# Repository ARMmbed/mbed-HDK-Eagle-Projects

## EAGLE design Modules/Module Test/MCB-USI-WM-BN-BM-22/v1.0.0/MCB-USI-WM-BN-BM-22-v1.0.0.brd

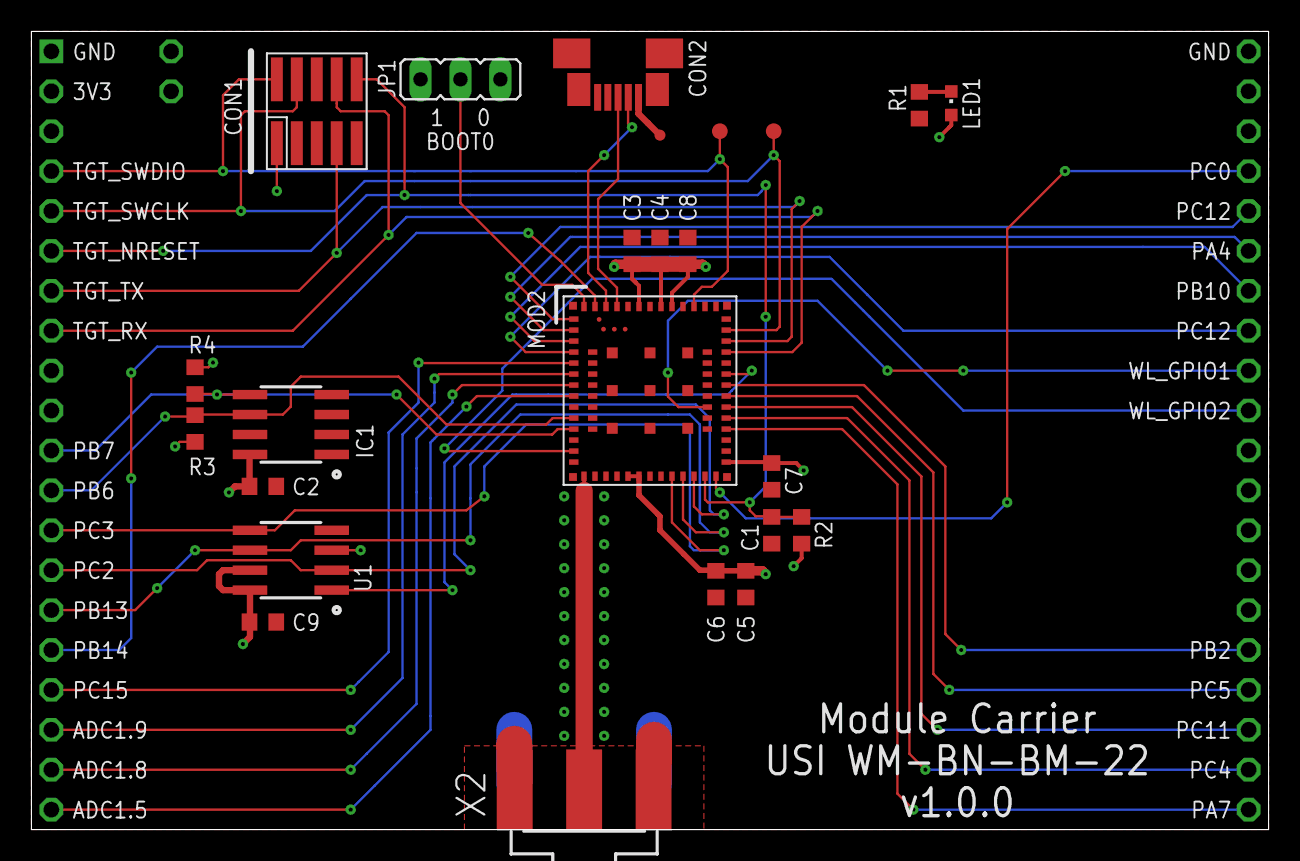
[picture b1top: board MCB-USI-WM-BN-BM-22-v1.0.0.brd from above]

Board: 2 copper layers, 78.7 x 50.8 mm, 28 parts (0 on the bottom side), 36 nets.

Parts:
C1, C2, C3, C4, C5, C6, C7, C8, C9: 100nF; 0603
CON1: SWD-10/TC2050_SMD; FTSH-105-02
CON2: 47346-0001; USB-MICRO-B-H
IC1: ATECC608A; SO8
JP1: BOOT0; JP2
LED1: RED; CHIPLED_0603
MOD1: MODULE_DAUGHTER
MOD2: USI-WM-BN-BM-22
R1: 1k; 0603
R2: 10k; 0603
R3, R4: 4k7; 0603
SS1: FLOSSICORN0.5; FLOSSICORN-0.5
TP1, TP2: TEST-POINT-50R-PTH; TP50-PTH
TP3, TP4: PTR1TP10R; TP10R
TP5: PTR1TP07R; TP07R
U1: MX25R3235FM1IH0; SO8
X2: SMA-142-0701-801/806; J502-ND-142-0701-801/806

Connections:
+3.3V_TGT: C2.1, C3.1, C4.1, C5.1, C6.1, C7.1, C8.1, C9.1, CON1.1, IC1.8, JP1.3, LED1.A, MOD1.2, MOD2.19, MOD2.20, MOD2.28, MOD2.46, MOD2.47, MOD2.49, R2.2, R3.2, R4.2, TP1.TP, U1.3, U1.7, U1.8
ADC1.5: MOD1.20, MOD2.8
ADC1.8: MOD1.19, MOD2.7
ADC1.9: MOD1.18, MOD2.6
BOOT0: JP1.2, MOD2.54
GND: C1.2, C2.2, C3.2, C4.2, C5.2, C6.2, C7.2, C8.2, C9.2, CON1.3, CON1.5, CON1.9, CON2.GND, IC1.4, JP1.1, MOD1.1, MOD1.40, MOD2.12, MOD2.14, MOD2.16, MOD2.17, MOD2.18, MOD2.21, MOD2.29, MOD2.30, MOD2.37, MOD2.45, MOD2.48, MOD2.50, MOD2.55, MOD2.56, MOD2.57, MOD2.58, MOD2.59, MOD2.60, MOD2.61, MOD2.62, MOD2.63, MOD2.64, MOD2.65, MOD2.66, MOD2.67, MOD2.68, MOD2.70, MOD2.74, MOD2.83, R1.1, TP2.TP, U1.4, X2.G@1, X2.G@2, X2.G@3, X2.G@4
unnamed: CON2.D+, MOD2.51
unnamed: CON2.D-, MOD2.52
unnamed: CON2.VBUS, TP5.TP
unnamed: MOD2.15, X2.1
PA4: MOD1.35, MOD2.2
PA6: MOD2.36, U1.1
PA7: MOD1.21, MOD2.31
PA_1: LED1.C, R1.2
PB2: MOD1.25, MOD2.35
PB6: IC1.6, MOD1.12, MOD2.10, R3.1
PB7: IC1.5, MOD1.11, MOD2.11, R4.1
PB10: MOD1.34, MOD2.3
PB12: MOD1.36, MOD2.1
PB13: MOD1.15, MOD2.24, U1.6
PB14: MOD1.16, MOD2.53
PC0: MOD1.37, MOD2.27
PC2: MOD1.14, MOD2.25, U1.2
PC3: MOD1.13, MOD2.23, U1.5
PC4: MOD1.22, MOD2.32
PC5: MOD1.24, MOD2.34
PC11: MOD1.23, MOD2.33
PC12: MOD1.33, MOD2.4
PC15: MOD1.17, MOD2.5
TGT_NRESET: C1.1, CON1.10, MOD1.6, MOD2.26, R2.1
TGT_RX: CON1.8, MOD1.8, MOD2.38
TGT_SWCLK: CON1.4, MOD1.5, MOD2.40, TP4.TP
TGT_SWDIO: CON1.2, MOD1.4, MOD2.44, TP3.TP
TGT_TX: CON1.7, MOD1.7, MOD2.39
WL_GPIO1: MOD1.32, MOD2.78
WL_GPIO2: MOD1.31, MOD2.13

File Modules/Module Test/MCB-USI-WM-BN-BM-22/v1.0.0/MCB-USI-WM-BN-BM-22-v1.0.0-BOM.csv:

"Qty";"Value";"Device";"Package";"Parts";"Description";"MF";"MFN";"MPN";"OC-DIGIKEY";"OC-MOUSER";"OC-NEWARK";"OC_FARNELL";"OC_NEWARK";"TP_SIGNAL_NAME";
"9";"100nF";"CAPACITOR0603";"0603";"C1, C2, C3, C4, C5, C6, C7, C8, C9";"Capacitor";"";"";"";"";"";"";"";"";"";
"1";"10k";"RESISTOR0603";"0603";"R2";"Resistor";"";"";"";"";"";"";"";"";"";
"1";"1k";"RESISTOR0603";"0603";"R1";"Resistor";"";"";"";"";"";"";"";"";"";
"1";"47346-0001";"47346-0001";"USB-MICRO-B-H";"CON2";"USB Receptacle Horizontal Micro Type B";"MOLEX";"47346-0001";"";"";"538-47346-0001";"1568026";"";"";"";
"2";"4k7";"RESISTOR0603";"0603";"R3, R4";"Resistor";"";"";"";"";"";"";"";"";"";
"1";"ATECC608A";"ATECC608A";"SO8";"IC1";"";"";"";"";"";"";"";"";"";"";
"1";"BOOT0";"JP2E";"JP2";"JP1";"JUMPER";"";"";"";"";"";"";"";"";"";
"1";"FLOSSICORN0.5";"FLOSSICORN0.5";"FLOSSICORN-0.5";"SS1";"";"";"";"";"";"";"";"";"";"";
"1";"MODULE_DAUGHTER";"MODULE_DAUGHTER";"MODULE_DAUGHTER";"MOD1";"";"";"";"";"";"";"";"";"";"";
"1";"MX25R3235FM1IH0";"MX25R3235FM1IH0";"SO8";"U1";"Serial Flash 32 Mb 80 Mhz";"Macronix";"MX25R3235FM2IH0";"";"1092-1174-ND";"";"";"";"";"";
"1";"PTR1TP07R";"PTR1TP07R";"TP07R";"TP5";"TEST PIN";"";"";"";"";"";"";"";"";"";
"2";"PTR1TP10R";"PTR1TP10R";"TP10R";"TP3, TP4";"TEST PIN";"";"";"";"";"";"";"";"";"";
"1";"RED";"SMD_LED0603";"CHIPLED_0603";"LED1";"LED SMD, Colour Red";"Wurth Electronics Inc";"150060RS75000";"";"732-4978-1-ND";"710-150060RS75000";"2322071";"";"";"";
"1";"SMA-142-0701-801/806";"SMA-142-0701-801/806";"J502-ND-142-0701-801/806";"X2";"SMA 50 Ohm End Launch Jack Receptacle - Round Contact";"JOHNSON COMPONENTS";"";"142-0701-801";"";"";"";"1608592";"90F2624";"";
"1";"SWD-10/TC2050_SMD";"SWD-10/TC2050_SMD";"FTSH-105-02";"CON1";"1mm pitch 10-Pin Cortex Programming Header with optional TC2050 footprint solderless interchangeable";"";"";"";"";"";"";"";"";"";
"2";"TEST-POINT-50R-PTH";"TEST-POINT-50R-PTH";"TP50-PTH";"TP1, TP2";"";"";"";"";"";"";"";"";"";"";
"1";"USI-WM-BN-BM-22";"USI-WM-BN-BM-22";"USI-WM-BN-BM-22";"MOD2";"";"";"";"";"";"";"";"";"";"";

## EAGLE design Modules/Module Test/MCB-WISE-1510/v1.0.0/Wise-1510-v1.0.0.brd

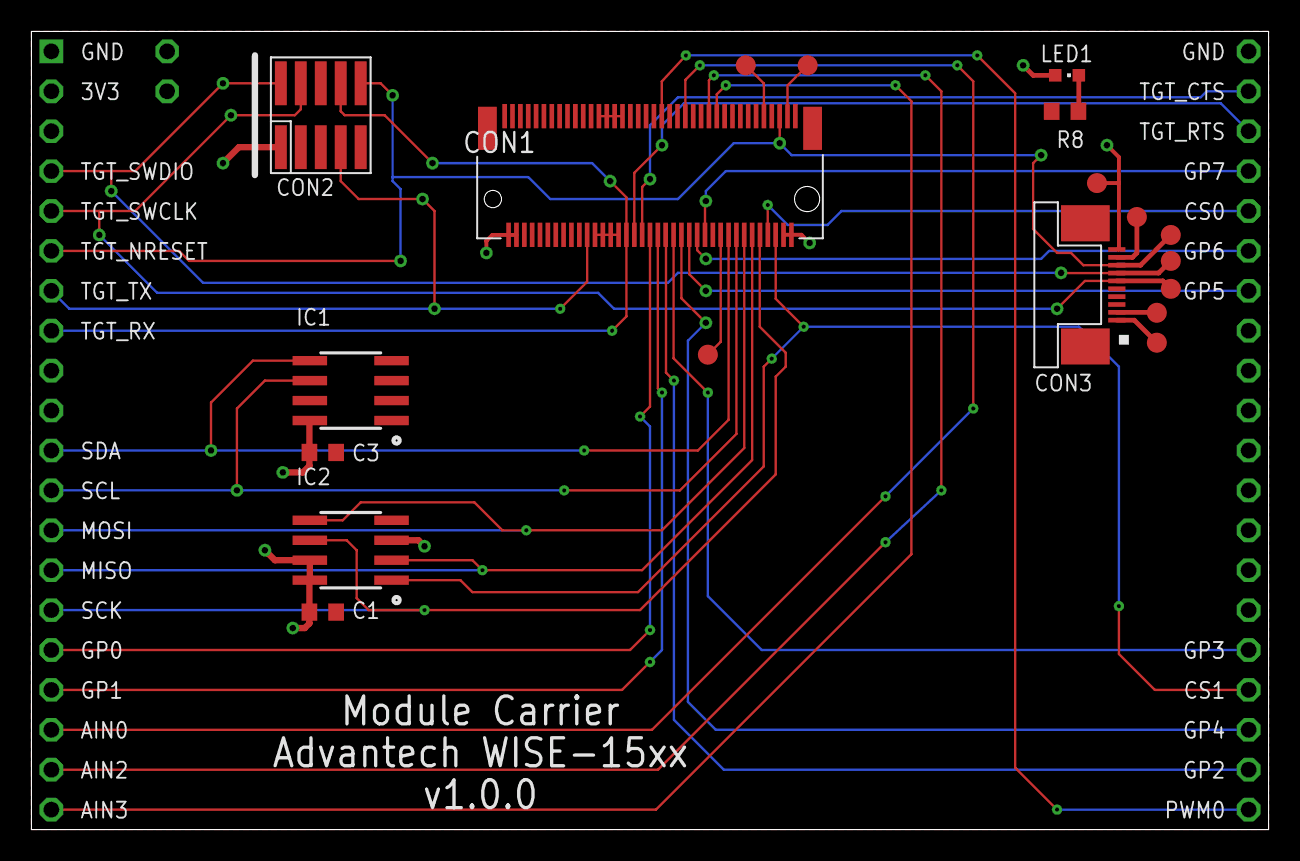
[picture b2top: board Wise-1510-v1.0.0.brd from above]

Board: 2 copper layers, 78.7 x 50.8 mm, 22 parts (0 on the bottom side), 36 nets.

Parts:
C1, C3: 100nF; 0603
CON1: WISE-1510_E; MDT420E02001
CON2: SWD-10/TC2050_SMD; FTSH-105-02
CON3: TE-1-1734592-0
IC1: ATECC608A; SO8
IC2: MX25R3235FM1IH0; SO8
LED1: RED; CHIPLED_0603
R8: 1k; 0603
TP1, TP2: TEST-POINT-50R-PTH; TP50-PTH
TP3, TP4, TP5, TP6, TP7, TP8, TP9, TP10, TP11, TP12: PTR1B1,27; B1,27
U$1: MODULE_DAUGHTER

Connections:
+3.3V_TGT: C1.1, C3.1, CON1.2, CON1.4, CON1.72, CON1.74, CON2.1, CON3.10, IC1.8, IC2.3, IC2.7, IC2.8, LED1.A, TP1.TP, TP12.TP, U$1.2
AIN0: CON1.47, U$1.18
AIN2: CON1.53, U$1.19
AIN3: CON1.55, U$1.20
BOOT_0: CON3.9, TP8.TP
CS0: CON1.68, U$1.36
CS1: CON1.70, IC2.1, U$1.24
GND: C1.2, C3.2, CON1.1, CON1.7, CON1.18, CON1.33, CON1.39, CON1.45, CON1.51, CON1.57, CON1.63, CON1.69, CON1.75, CON1.H1, CON1.H2, CON2.3, CON2.5, CON2.9, CON3.3, IC1.4, IC2.4, R8.1, TP2.TP, U$1.1, U$1.40
GP0: CON1.38, U$1.16
GP1: CON1.40, U$1.17
GP2: CON1.42, U$1.22
GP3: CON1.44, U$1.25
GP4: CON1.46, U$1.23
GP5: CON1.48, U$1.34
GP6: CON1.50, U$1.35
GP7: CON1.52, U$1.37
KEY: CON1.24, CON1.25, CON1.26, CON1.27, CON1.28, CON1.29, CON1.30, CON1.31
MISO: CON1.64, IC2.2, U$1.14
MOSI: CON1.62, IC2.5, U$1.13
unnamed: CON3.1, TP7.TP
unnamed: CON3.2, TP6.TP
unnamed: CON1.56, TP9.TP
unnamed: CON1.67, TP10.TP
unnamed: CON1.73, TP11.TP
PA_1: LED1.C, R8.2
PWM0: CON1.41, U$1.21
SCK: CON1.66, IC2.6, U$1.15
SCL: CON1.60, IC1.6, U$1.12
SDA: CON1.58, IC1.5, U$1.11
TGT_CTS: CON1.36, U$1.39
TGT_NRESET: CON1.71, CON2.10, CON3.8, TP5.TP, U$1.6
TGT_RTS: CON1.34, U$1.38
TGT_RX: CON1.32, CON2.8, U$1.8
TGT_SWCLK: CON2.4, CON3.6, TP3.TP, U$1.5
TGT_SWDIO: CON2.2, CON3.7, TP4.TP, U$1.4
TGT_TX: CON1.22, CON2.7, U$1.7

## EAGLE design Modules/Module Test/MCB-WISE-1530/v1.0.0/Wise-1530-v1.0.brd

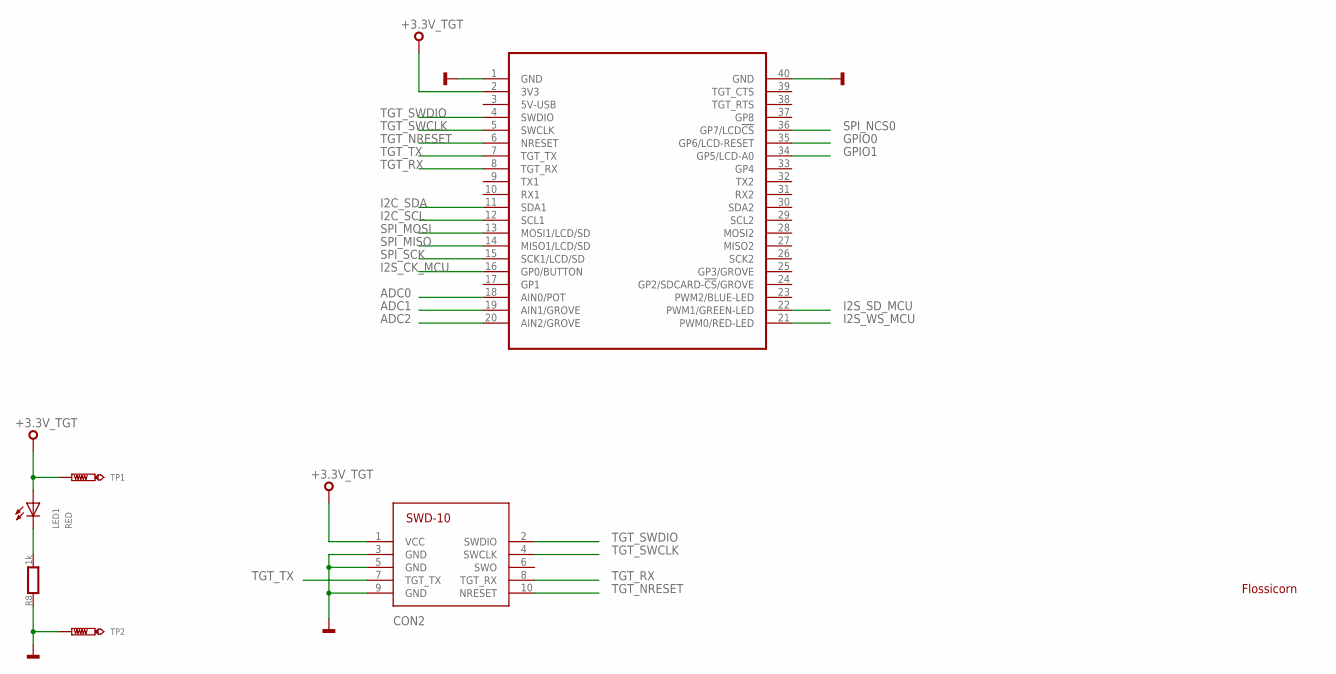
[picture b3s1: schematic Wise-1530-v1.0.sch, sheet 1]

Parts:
CON2: SWD-10/TC2050_SMD; FTSH-105-02
LED1: RED; CHIPLED_0603
MOD2: MODULE_DAUGHTER
R8: 1k; 0603
SS1: FLOSSICORN0.25; FLOSSICORN-0.25
TP1, TP2: TEST-POINT-50R-PTH; TP50-PTH

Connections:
+3.3V_TGT: CON2.1 (VCC), LED1.A, MOD2.2 (3V3), TP1.TP; also elsewhere on the board
ADC0: MOD2.18 (AIN0/POT); also elsewhere on the board
ADC1: MOD2.19 (AIN1/GROVE); also elsewhere on the board
ADC2: MOD2.20 (AIN2/GROVE); also elsewhere on the board
GND: CON2.3 (GND), CON2.5 (GND), CON2.9 (GND), MOD2.1 (GND), MOD2.40 (GND), R8.1, TP2.TP; also elsewhere on the board
GPIO0: MOD2.35 (GP6/LCD-RESET); also elsewhere on the board
GPIO1: MOD2.34 (GP5/LCD-A0); also elsewhere on the board
I2C_SCL: MOD2.12 (SCL1); also elsewhere on the board
I2C_SDA: MOD2.11 (SDA1); also elsewhere on the board
I2S_CK_MCU: MOD2.16 (GP0/BUTTON); also elsewhere on the board
I2S_SD_MCU: MOD2.22 (PWM1/GREEN-LED); also elsewhere on the board
I2S_WS_MCU: MOD2.21 (PWM0/RED-LED); also elsewhere on the board
PA_1: LED1.C, R8.2
SPI_MISO: MOD2.14 (MISO1/LCD/SD); also elsewhere on the board
SPI_MOSI: MOD2.13 (MOSI1/LCD/SD); also elsewhere on the board
SPI_NCS0: MOD2.36 (GP7/LCD!CS); also elsewhere on the board
SPI_SCK: MOD2.15 (SCK1/LCD/SD); also elsewhere on the board
TGT_NRESET: CON2.10 (NRESET), MOD2.6 (NRESET); also elsewhere on the board
TGT_RX: CON2.8 (TGT_RX), MOD2.8 (TGT_RX); also elsewhere on the board
TGT_SWCLK: CON2.4 (SWCLK), MOD2.5 (SWCLK); also elsewhere on the board
TGT_SWDIO: CON2.2 (SWDIO), MOD2.4 (SWDIO); also elsewhere on the board
TGT_TX: CON2.7 (TGT_TX), MOD2.7 (TGT_TX); also elsewhere on the board

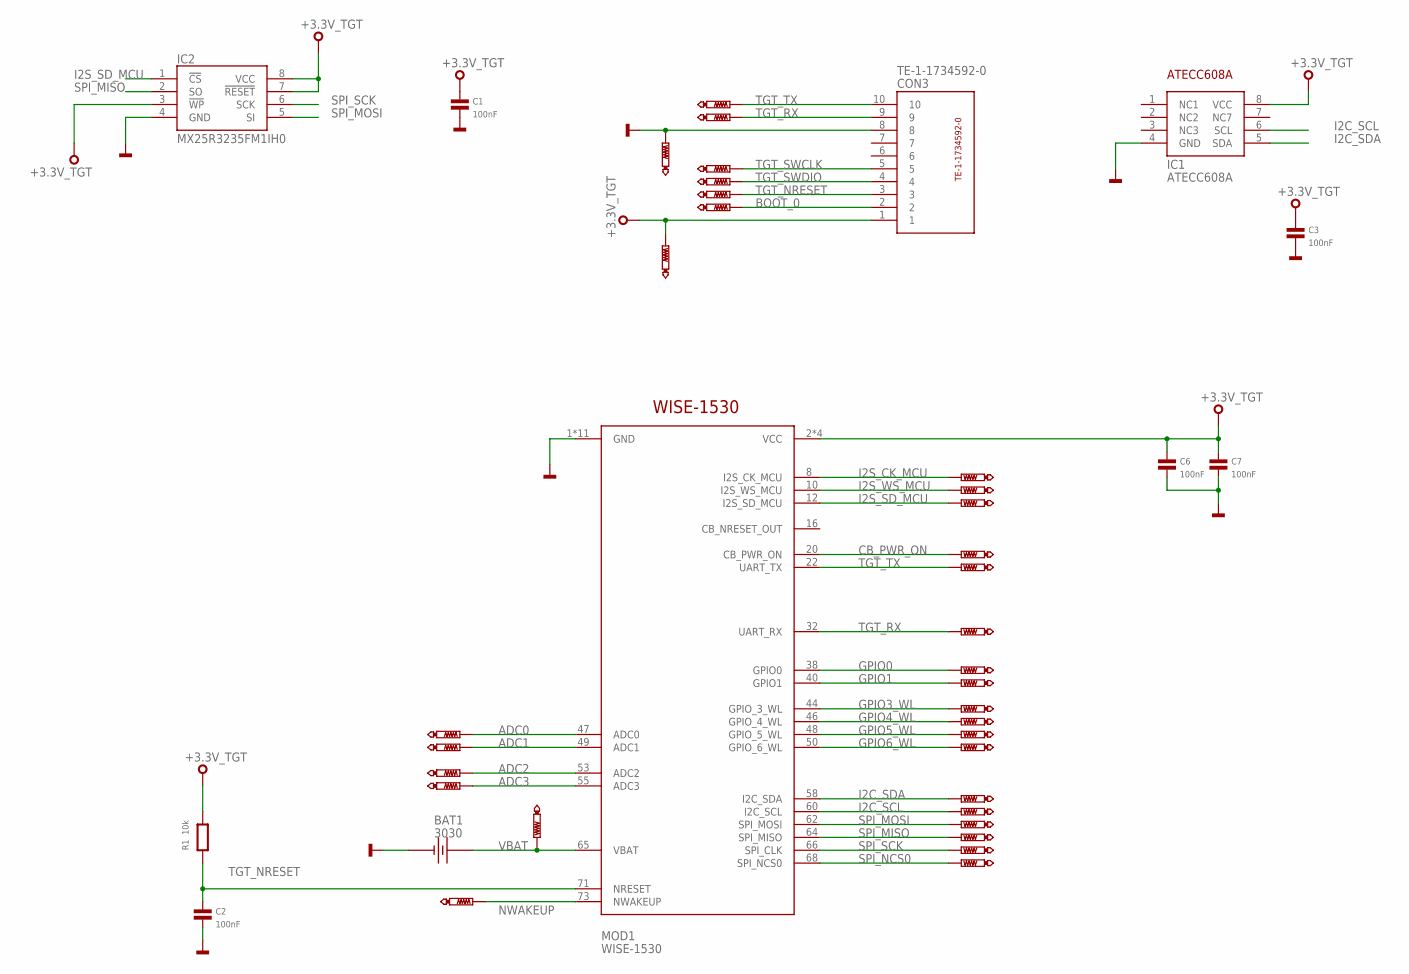
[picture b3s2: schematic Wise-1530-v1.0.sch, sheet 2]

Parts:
BAT1: 3030
C1, C2, C3, C6, C7: 100nF; 0603
CON3: TE-1-1734592-0
IC1: ATECC608A; SO8
IC2: MX25R3235FM1IH0; SO8
MOD1: WISE-1530; MDT420E02001
R1: 10k; 0603
TP3, TP4, TP5, TP6, TP7, TP8, TP12, TP13: PTR1TP08R; TP08R
TP9, TP10, TP11, TP14, TP15, TP16, TP17, TP18, TP19, TP20, TP21, TP22, TP23, TP24, TP25, TP26, TP27, TP28, TP29, TP30, TP31, TP32, TP33, TP34: PTR1TP07R; TP07R

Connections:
+3.3V_TGT: C1.1, C3.1, C6.1, C7.1, CON3.1, IC1.8 (VCC), IC2.3 (!WP), IC2.7 (!RESET), IC2.8 (VCC), MOD1.2 (VCC), MOD1.4 (VCC), MOD1.72 (VCC), MOD1.74 (VCC), R1.2, TP12.TP; also elsewhere on the board
ADC0: MOD1.47 (ADC0), TP29.TP; also elsewhere on the board
ADC1: MOD1.49 (ADC1), TP30.TP; also elsewhere on the board
ADC2: MOD1.53 (ADC2), TP31.TP; also elsewhere on the board
ADC3: MOD1.55 (ADC3), TP32.TP
BOOT_0: CON3.2, TP8.TP
CB_PWR_ON: MOD1.20 (CB_PWR_ON), TP14.TP
GND: BAT1.-, C1.2, C2.2, C3.2, C6.2, C7.2, CON3.8, IC1.4 (GND), IC2.4 (GND), MOD1.1 (GND), MOD1.7 (GND), MOD1.18 (GND), MOD1.33 (GND), MOD1.39 (GND), MOD1.45 (GND), MOD1.51 (GND), MOD1.57 (GND), MOD1.63 (GND), MOD1.69 (GND), MOD1.75 (GND), TP13.TP; also elsewhere on the board
GPIO0: MOD1.38 (GPIO0), TP27.TP; also elsewhere on the board
GPIO1: MOD1.40 (GPIO1), TP26.TP; also elsewhere on the board
GPIO3_WL: MOD1.44 (GPIO_3_WL), TP25.TP
GPIO4_WL: MOD1.46 (GPIO_4_WL), TP24.TP
GPIO5_WL: MOD1.48 (GPIO_5_WL), TP23.TP
GPIO6_WL: MOD1.50 (GPIO_6_WL), TP22.TP
I2C_SCL: IC1.6 (SCL), MOD1.60 (I2C_SCL), TP20.TP; also elsewhere on the board
I2C_SDA: IC1.5 (SDA), MOD1.58 (I2C_SDA), TP21.TP; also elsewhere on the board
I2S_CK_MCU: MOD1.8 (I2S_CK_MCU), TP9.TP; also elsewhere on the board
I2S_SD_MCU: IC2.1 (!CS), MOD1.12 (I2S_SD_MCU), TP11.TP; also elsewhere on the board
I2S_WS_MCU: MOD1.10 (I2S_WS_MCU), TP10.TP; also elsewhere on the board
NWAKEUP: MOD1.73 (NWAKEUP), TP34.TP
SPI_MISO: IC2.2 (SO), MOD1.64 (SPI_MISO), TP18.TP; also elsewhere on the board
SPI_MOSI: IC2.5 (SI), MOD1.62 (SPI_MOSI), TP19.TP; also elsewhere on the board
SPI_NCS0: MOD1.68 (SPI_NCS0), TP16.TP; also elsewhere on the board
SPI_SCK: IC2.6 (SCK), MOD1.66 (SPI_CLK), TP17.TP; also elsewhere on the board
TGT_NRESET: C2.1, CON3.3, MOD1.71 (NRESET), R1.1, TP5.TP; also elsewhere on the board
TGT_RX: CON3.9, MOD1.32 (UART_RX), TP6.TP, TP28.TP; also elsewhere on the board
TGT_SWCLK: CON3.5, TP3.TP; also elsewhere on the board
TGT_SWDIO: CON3.4, TP4.TP; also elsewhere on the board
TGT_TX: CON3.10, MOD1.22 (UART_TX), TP7.TP, TP15.TP; also elsewhere on the board
VBAT: BAT1.+1 (+), BAT1.+2 (+), MOD1.65 (VBAT), TP33.TP

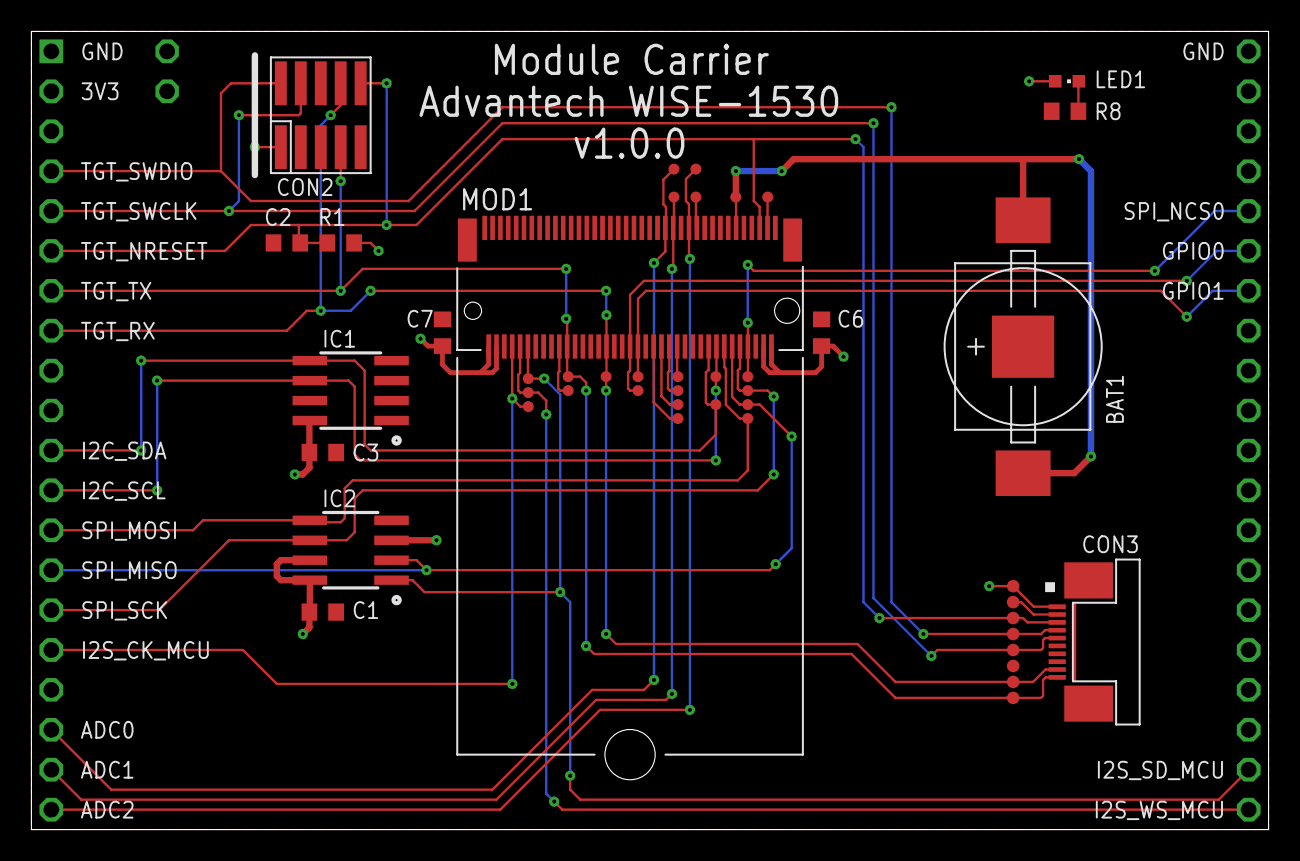
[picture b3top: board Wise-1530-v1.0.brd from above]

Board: 2 copper layers, 78.7 x 50.8 mm, 50 parts (0 on the bottom side), 31 nets.

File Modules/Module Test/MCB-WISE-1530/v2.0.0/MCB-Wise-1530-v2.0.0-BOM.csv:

"Qty";"Value";"Device";"Package";"Parts";"Description";"MF";"MFN";"OC-DIGIKEY";"OC-MOUSER";"OC-NEWARK";"TP_SIGNAL_NAME";
"5";"100nF";"CAPACITOR0603";"0603";"C1, C2, C3, C6, C7";"Capacitor";"";"";"";"";"";"";
"1";"10k";"RESISTOR0603";"0603";"R1";"Resistor";"";"";"";"";"";"";
"1";"1k";"RESISTOR0603";"0603";"R8";"Resistor";"";"";"";"";"";"";
"1";"3030";"3030";"3030";"BAT1";"CR927, CR1025 Battery Holder for 9-10mm Cells-Tin Nickel Plated SMD";"Keystone";"3030";"36-3030-ND";"534-3030";"39T8899";"";
"1";"ATECC608A";"ATECC608A";"SO8";"IC1";"";"";"";"";"";"";"";
"1";"FLOSSICORN0.25";"FLOSSICORN0.25";"FLOSSICORN-0.25";"SS1";"";"";"";"";"";"";"";
"1";"MODULE_DAUGHTER";"MODULE_DAUGHTER";"MODULE_DAUGHTER";"MOD2";"";"";"";"";"";"";"";
"1";"MX25R3235FM1IH0";"MX25R3235FM1IH0";"SO8";"IC2";"Serial Flash 32 Mb 80 Mhz";"Macronix";"MX25R3235FM1IH0";"1092-1175-ND";"";"";"";
"24";"PTR1TP07R";"PTR1TP07R";"TP07R";"TP9, TP10, TP11, TP14, TP15, TP16, TP17, TP18, TP19, TP20, TP21, TP22, TP23, TP24, TP25, TP26, TP27, TP28, TP29, TP30, TP31, TP32, TP33, TP34";"TEST PIN";"";"";"";"";"";"";
"8";"PTR1TP08R";"PTR1TP08R";"TP08R";"TP3, TP4, TP5, TP6, TP7, TP8, TP12, TP13";"TEST PIN";"";"";"";"";"";"";
"1";"RED";"SMD_LED0603";"CHIPLED_0603";"LED1";"LED SMD, Colour Red";"Wurth Electronics Inc";"150060RS75000";"732-4978-1-ND";"710-150060RS75000";"2322071";"";
"1";"SWD-10/TC2050_SMD";"SWD-10/TC2050_SMD";"FTSH-105-02";"CON2";"1mm pitch 10-Pin Cortex Programming Header with optional TC2050 footprint solderless interchangeable";"";"";"";"";"";"";
"1";"TE-1-1734592-0";"TE-1-1734592-0";"TE-1-1734592-0";"CON3";"";"";"";"";"";"";"";
"2";"TEST-POINT-50R-PTH";"TEST-POINT-50R-PTH";"TP50-PTH";"TP1, TP2";"";"";"";"";"";"";"";
"1";"WISE-1530";"WISE-1530";"MDT420E02001";"MOD1";"";"";"";"";"";"";"";

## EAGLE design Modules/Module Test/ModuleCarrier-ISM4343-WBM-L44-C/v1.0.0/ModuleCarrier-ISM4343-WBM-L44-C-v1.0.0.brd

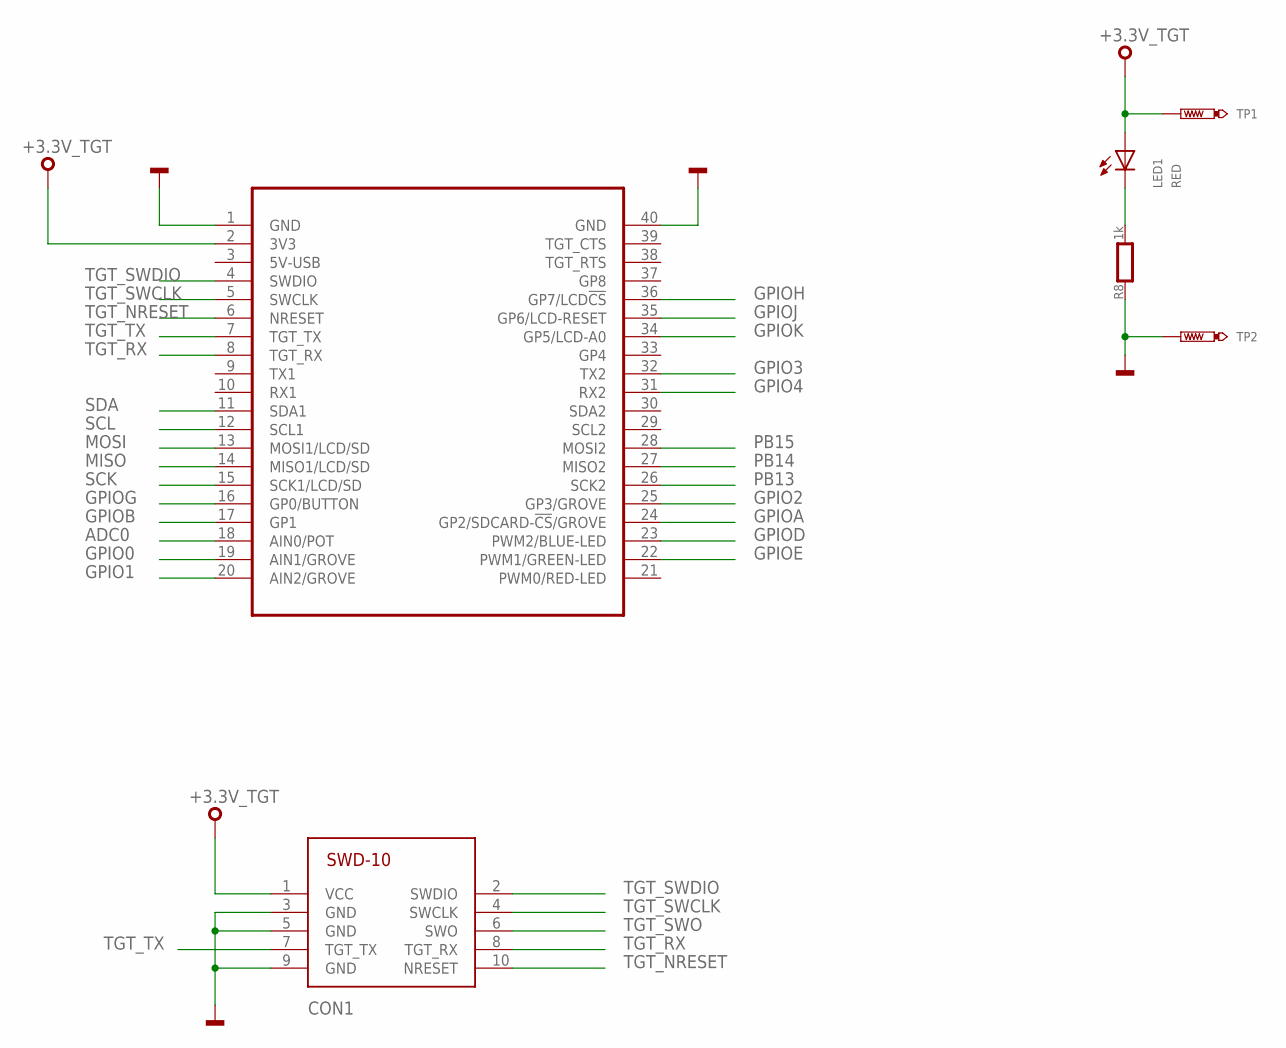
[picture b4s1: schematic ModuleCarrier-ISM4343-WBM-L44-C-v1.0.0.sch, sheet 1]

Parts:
CON1: SWD-10/TC2050_SMD; FTSH-105-02
LED1: RED; CHIPLED_0603
MOD2: MODULE_DAUGHTER
R8: 1k; 0603
TP1, TP2: TEST-POINT-50R-PTH; TP50-PTH

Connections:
+3.3V_TGT: CON1.1 (VCC), LED1.A, MOD2.2 (3V3), TP1.TP; also elsewhere on the board
ADC0: MOD2.18 (AIN0/POT)
GND: CON1.3 (GND), CON1.5 (GND), CON1.9 (GND), MOD2.1 (GND), MOD2.40 (GND), R8.1, TP2.TP; also elsewhere on the board
GPIO0: MOD2.19 (AIN1/GROVE)
GPIO1: MOD2.20 (AIN2/GROVE)
GPIO2: MOD2.25 (GP3/GROVE)
GPIO3: MOD2.32 (TX2)
GPIO4: MOD2.31 (RX2)
GPIOA: MOD2.24 (GP2/SDCARD-!CS!/GROVE)
GPIOB: MOD2.17 (GP1)
GPIOD: MOD2.23 (PWM2/BLUE-LED)
GPIOE: MOD2.22 (PWM1/GREEN-LED)
GPIOG: MOD2.16 (GP0/BUTTON)
GPIOH: MOD2.36 (GP7/LCD!CS)
GPIOJ: MOD2.35 (GP6/LCD-RESET)
GPIOK: MOD2.34 (GP5/LCD-A0)
MISO: MOD2.14 (MISO1/LCD/SD); also elsewhere on the board
MOSI: MOD2.13 (MOSI1/LCD/SD); also elsewhere on the board
PA_1: LED1.C, R8.2
PB13: MOD2.26 (SCK2)
PB14: MOD2.27 (MISO2)
PB15: MOD2.28 (MOSI2)
SCK: MOD2.15 (SCK1/LCD/SD); also elsewhere on the board
SCL: MOD2.12 (SCL1); also elsewhere on the board
SDA: MOD2.11 (SDA1); also elsewhere on the board
TGT_NRESET: CON1.10 (NRESET), MOD2.6 (NRESET)
TGT_RX: CON1.8 (TGT_RX), MOD2.8 (TGT_RX)
TGT_SWCLK: CON1.4 (SWCLK), MOD2.5 (SWCLK)
TGT_SWDIO: CON1.2 (SWDIO), MOD2.4 (SWDIO)
TGT_SWO: CON1.6 (SWO)
TGT_TX: CON1.7 (TGT_TX), MOD2.7 (TGT_TX)

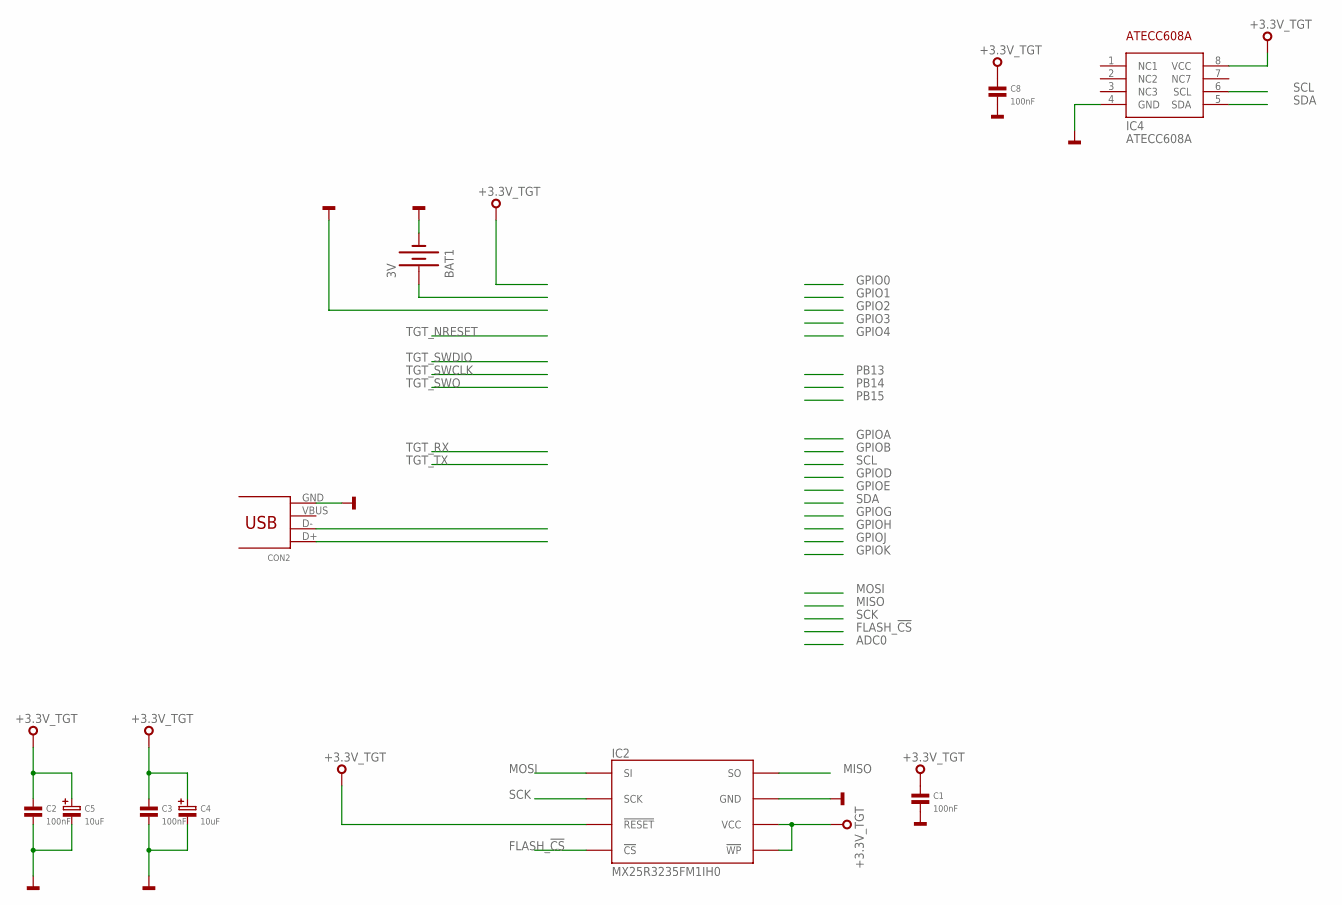
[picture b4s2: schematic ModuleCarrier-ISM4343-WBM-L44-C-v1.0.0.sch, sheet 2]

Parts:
BAT1: 3V; BATTCON_12MM
C1, C2, C3, C8: 100nF; 0603
C4, C5: 10uF; SMC_B
CON2: 10033526-N3212MLF; USB-MINI-B-H
IC2: MX25R3235FM1IH0; SO8
IC4: ATECC608A; SO8

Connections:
+3.3V_TGT: C1.1, C2.1, C3.1, C4.+, C5.+, C8.1, IC2.3 (!WP), IC2.7 (!RESET), IC2.8 (VCC), IC4.8 (VCC); also elsewhere on the board
FLASH_!CS: IC2.1 (!CS)
GND: BAT1.GND (-), C1.2, C2.2, C3.2, C4.-, C5.-, C8.2, CON2.GND, IC2.4 (GND), IC4.4 (GND); also elsewhere on the board
MISO: IC2.2 (SO); also elsewhere on the board
MOSI: IC2.5 (SI); also elsewhere on the board
SCK: IC2.6 (SCK); also elsewhere on the board
SCL: IC4.6 (SCL); also elsewhere on the board
SDA: IC4.5 (SDA); also elsewhere on the board

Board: 2 copper layers, 16 parts (0 on the bottom side), 13 nets, no tracks yet.

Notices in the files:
parts and their libraries:
SparkFun-Electromechanical: Licensing: CC v3.0 Share-Alike You are welcome to use this library for commercial purposes.
